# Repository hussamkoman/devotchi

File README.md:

<h1 align="center">Devotchi</h1>

<p align="center">
  <b>A desk pet for your coding agent.</b><br>
  See what Claude Code is doing and answer it with three buttons.
</p>

When Claude Code needs you, Devotchi buzzes and shows the request. You allow,
deny or answer from across the desk. Between requests, its pet shows how the
work is going.

> Devotchi never decides on its own. Only a button press allows or denies.
> If nobody answers, Claude Code's normal terminal prompt takes over.

## Features

- **Approvals.** See the exact command and its risk. Allow, deny, allow for this
  session, or send it to the terminal. High-risk commands need a hold.
- **Questions and plans.** Answer Claude's questions and approve or revise its plans.
- **A pet with moods.** 11 moods and 5 reactions, driven by Claude Code hooks.
- **Clock face** while idle, **Showcase mode** for demos, real **sleep modes**
  and battery support.
- **Self-hosted.** A small server on your PC, a local dashboard, optional
  multi-user hosting.

## Screens

<table>
  <tr>
    <td align="center"><br><sub>Decision menu</sub></td>
    <td align="center"><br><sub>Question from Claude</sub></td>
    <td align="center"><br><sub>Plan approval</sub></td>
  </tr>
  <tr>
    <td align="center"><br><sub>Tests passed</sub></td>
    <td align="center"><br><sub>Clock face</sub></td>
    <td align="center"><br><sub>Settings</sub></td>
  </tr>
</table>

Screenshots are taken from the real device. The full design is in [docs/design](docs/design/index.html).

## Pets

Each pet is one JSON file in [`pets/`](pets/README.md). Adding a pet needs no code.

| | |
|---|---|
|  | **Devo** (default)<br>The ghost from the PCB silkscreen. Its antenna and chip light show the mood. |
|  | **Mochi**<br>A soft square with an antenna. |
|  | **Ember**<br>A small jade dragon. Wings, tail, smoke and fire show the mood. |
|  | **Sprout**<br>An egg with a leaf. Install it from the dashboard. |

Shown in the happy, focused and sleeping moods.

## How it works

```
Claude Code ──hooks──▶ Devotchi server ──Wi-Fi──▶ Devotchi device
  (your PC)            (Node, SQLite)              (ESP32-S3 + LCD)
                            │
                            └──▶ dashboard (browser)
```

1. `devotchi setup` adds HTTP hooks to Claude Code.
2. Requests go to the server, which shows them on the device and the dashboard.
3. You press a button. The device sends a heartbeat while it shows a request,
   so the server knows it is alive.
4. If nobody answers in time (default 30 s), or no device is online, Claude
   Code shows its own prompt.

## Quick start

Needs Node 22.13+ and pnpm 10.

```bash
pnpm install && pnpm run build
alias devotchi="node $PWD/packages/client/dist/cli.js"

devotchi start --local --lan   # server on :8080, dashboard on 127.0.0.1:3456
devotchi setup                 # add the hooks to this project
```

Then set up the device:

1. **Wi-Fi:** install the **ESP BLE Provisioning** app and scan the QR code
   *inside the app*. Your phone's camera app can't do this.
2. **Server:** the device connects to `ws://<your PC>:8080`. Change it with
   `server ws://<ip>:8080` on the USB console.
3. **Pair:** run `devotchi pair <CODE>` with the code on the screen.

For a hosted server with TLS and accounts, see [docs/deploy.md](docs/deploy.md).

## Buttons

| | Left | Middle | Right |
|---|---|---|---|
| **Home** | Poke | Recent activity · hold: menu | Pat |
| **Request** | Deny | Hold: more options | Allow (high risk: hold) |
| **Settings** | Up · hold: back | Next | Open |

Any press wakes the device and does nothing else.

## CLI

```bash
devotchi start | setup | pair <CODE> | status | doctor
devotchi devices | pets | mode [ask|desk] | hold [seconds]
devotchi notify <event> | run -- <cmd> | sim | mcp | login | config
```

Run `devotchi doctor` when something doesn't work. Full list: [CLAUDE.md](CLAUDE.md#client-cli).

## Hardware

- ESP32-S3-MINI-1 (Wi-Fi, BLE, 4 MB flash, 2 MB PSRAM)
- 2.0" 320x240 IPS display (ST7789)
- 3 buttons, vibration motor, status LED
- LiPo battery with USB-C charging

Details: [hardware/README.md](hardware/README.md).

<br clear="right">

## Development

```bash
pnpm test && pnpm run typecheck && pnpm run lint
```

The firmware is plain C on ESP-IDF 6.0 with LVGL 9. Building, flashing and
tests: [firmware/README.md](firmware/README.md).

| Folder | What's in it |
|---|---|
| `firmware/` | ESP32-S3 firmware and host tests |
| `packages/` | `shared` protocol, `server`, `client` (CLI, MCP, dashboard) |
| `pets/` | Pet JSON files |
| `docs/` | [Architecture](docs/architecture.md), [protocol](docs/protocol.md), [design](docs/design/index.html) |
| `hardware/`, `case/` | PCB and enclosure |

Open work: [TODO.md](TODO.md).

## License

[MIT](LICENSE)

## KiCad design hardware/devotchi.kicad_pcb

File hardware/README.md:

# Hardware Design

## PCB

## Device Variants

### Portable WiFi+BLE (current)
- ESP32-S3-MINI-1 with integrated PCB antenna
- HS20HS072RX 2.0" color TFT LCD (ST7789, 320x240, IPS)
- LiPo battery, USB-C charging
- 3 buttons (approve, reject, action)
- Status LED, vibration motor
- Connects to server via WiFi, or to phone via BLE

### Portable Cellular (planned)
- Same form factor as WiFi+BLE version
- Additional cellular modem (MCU TBD — may use same ESP32-S3 + SIM module, or different MCU)
- SIM/eSIM support (provider TBD)
- Works standalone anywhere with cell coverage

### Desktop (planned)
- USB-powered (no battery needed)
- Potentially larger display
- Same ESP32-S3-MINI-1, connects via USB serial or WiFi

---

## Parts

See [purchase-list.md](purchase-list.md) for the complete BOM with LCSC part numbers and sourcing info.

### MCU: ESP32-S3-MINI-1-N4R2

| Spec | Value |
|---|---|
| Part number | ESP32-S3-MINI-1-N4R2 (4MB flash, 2MB PSRAM) |
| CPU | Dual-core Xtensa LX7 @ 240 MHz |
| SRAM | 512 KB + 2MB PSRAM |
| WiFi | 802.11 b/g/n, 2.4 GHz |
| Bluetooth | BLE 5.0 |
| Antenna | Integrated PCB antenna |
| Module dimensions | 15.4 x 20.5 x 2.4 mm |
| Operating voltage | 3.0 - 3.6V |

**Datasheets:** [Module](../docs/mcu/ESP32-S3-MINI-1_datasheet.pdf) | [SoC](../docs/mcu/ESP32-S3_SoC_datasheet.pdf)

**Why N4R2:** PSRAM needed for display framebuffers — 320x240 RGB565 = 150KB per frame, double buffering needs 300KB. Without PSRAM, internal 512KB SRAM can't fit framebuffers + WiFi stack + application.

### Display: HS20HS072RX 2.0" Color TFT LCD

| Spec | Value |
|---|---|
| Manufacturer | HS (Shenzhen Hansheng) |
| Part number | HS20HS072RX |
| LCSC | C5329582 |
| Driver IC | ST7789T3 |
| Size | 2.0 inches diagonal |
| Resolution | 320 x 240 pixels (QVGA) |
| Colors | 262K (RGB666) |
| Pixel pitch | 0.151 x 0.153 mm |
| Active area | 40.80 x 30.60 mm |
| Module size | 51.80 x 36.20 mm |
| Interface | SPI (4-wire) |
| Operating voltage | IOVCC 1.65-3.3V, VCI 2.4-3.3V |
| Backlight | 4 white LEDs in parallel, 80mA max |
| Backlight forward voltage | 3.0V typical (2.8-3.2V) |
| Sleep current | ~30 uA (SLPIN command) |
| Viewing angle | ALL directions (IPS) |
| Contrast ratio | 300:1 typical |
| Connector | 12-pin FPC, 0.5mm pitch |
| Connection type | COG + FPC |

**Datasheet:** [HS20HS072RX datasheet](../docs/display/HS20HS072RX_datasheet.pdf)

**Source:** [LCSC/JLCPCB C5329582](https://www.lcsc.com/product-detail/lcd-screen_hs-hs20hs072rx_C5329582.html) — $3.70 (1+), $2.49 (100+), 1687 in stock.

**Why this part:**
- Full RGB color — expressive Tamagotchi character (red angry, green happy, etc.)
- 320x240 resolution — excellent detail for pixel art and text
- IPS viewing angle — looks good from any direction (critical for handheld)
- Runs entirely on 3.3V — no boost converter needed (unlike OLED panels needing 12V VCC)
- ST7789 has first-class ESP-IDF support via built-in `esp_lcd` driver
- $2.49 at volume with 1600+ stock — cheap and available
- 12-pin FPC is simple to wire (vs 30-pin for OLED panels)
- Backlight can be PWM-dimmed via MOSFET for power saving

**FPC pinout:**

| Pin | Symbol | Description |
|---|---|---|
| 1 | GND | Power ground |
| 2 | CS | Chip select (active low) |
| 3 | RS (DC) | Data/command select |
| 4 | SCL | SPI clock |
| 5 | SDA | SPI data (MOSI) |
| 6 | RST | Reset (active low) |
| 7 | NC | No connect |
| 8 | IOVCC | I/O logic supply (3.3V) |
| 9 | VCC | Panel power supply (3.3V) |
| 10 | A | Backlight LED anode |
| 11 | K | Backlight LED cathode |
| 12 | GND | Power ground |

### Backlight Dimming Circuit

Backlight driven from +BATT (3.7-4.2V) through 22Ω resistor + AO3400A N-ch MOSFET, PWM-controlled by ESP32.

**Why +BATT instead of 3.3V:** LEDs have Vf = 3.0V. Only 0.3V headroom from 3.3V — poor regulation. +BATT gives 0.7-1.2V headroom.

**Circuit:** `+BATT → R (22Ω) → LED anode → LED cathode → MOSFET drain → GND`, gate driven by DISP_BL GPIO.

**Current at different battery voltages:**
- 4.2V (full): ~55mA | 3.7V (nominal): ~32mA | 3.4V (low): ~18mA

**Firmware:** PWM at 1kHz+. Sleep: SLPIN (0x10) + duty=0. Wake: duty>0 + SLPOUT (0x11), wait 120ms.

### Firmware Graphics Library

**Recommended: ESP-IDF native `esp_lcd` + LovyanGFX**

- `esp_lcd` provides the built-in ST7789 panel driver for SPI initialization
- LovyanGFX provides sprite-based graphics, text rendering, and animations
- LovyanGFX supports ESP-IDF natively (not Arduino-only)
- Supports DMA transfers for background rendering
- ST7789 sleep commands (SLPIN/SLPOUT) supported for power management
- Alternative: LVGL if more complex UI widgets are needed later

### Power Chain

USB-C → TP4056 (charger) → DW01A+FS8205A (protection) → ME6211 (3.3V LDO) → ESP32-S3 + display

**Datasheets:** [TP4056](../docs/power/TP4056_datasheet.pdf) | [DW01A](../docs/power/DW01A_datasheet.pdf) | [FS8205A](../docs/power/FS8205A_datasheet.pdf) | [ME6211](../docs/power/ME6211_datasheet.pdf)

**Key design notes:**
- TP4056 charge current set by R205 (3kΩ → ~330mA charge rate)
- DW01A+FS8205A: standard LiPo protection pair, back-to-back MOSFETs in battery ground path
- ME6211 LDO: 100mV dropout — at low battery (<3.4V) output sags below 3.3V, acceptable for MVP
- USB-C CC1/CC2 pull-downs: 5.1kΩ each for proper USB-C detection

### Buttons

3 tactile switches with hardware debounce (10kΩ pull-up + 100nF cap per button). Active low, pressed = GND. Any button press wakes from deep sleep.

| Button | Function |
|---|---|
| Approve | Accept approval/permission requests |
| Reject | Reject approval/permission requests |
| Action | Context-dependent: scroll, open menu, poke pet |

### Feedback

- **Debug LED** (green 0603) — GPIO direct drive through 150Ω resistor. Dev/debug only.
- **Vibration motor** (6mm coin, 3V) — AO3400A MOSFET driver + 1N5819W flyback diode. PWM-capable. Connected via solder pads.

---

## Pin Assignment

**Strapping pins to avoid:** GPIO0 (boot mode), GPIO3 (JTAG source, floating), GPIO45 (VDD_SPI), GPIO46 (boot mode). These are sampled at reset and should not have external loads that could affect their default state during boot.

| Function | ESP32-S3 GPIO | Notes |
|---|---|---|
| **SPI Display** | | |
| DISP_SCLK | GPIO 12 | SPI clock |
| DISP_MOSI | GPIO 11 | SPI data |
| DISP_CS | GPIO 10 | Chip select |
| DISP_DC | GPIO 9 | Data/command select |
| DISP_RST | GPIO 8 | Reset |
| DISP_BL | GPIO 13 | PWM via MOSFET to backlight cathode |
| **Buttons** | | |
| BTN_APPROVE | GPIO 4 | Pull-up, active low |
| BTN_REJECT | GPIO 5 | Pull-up, active low |
| BTN_ACTION | GPIO 6 | Pull-up, active low |
| **Feedback** | | |
| LED_PWM | GPIO 38 | PWM for brightness control |
| MOTOR_EN | GPIO 37 | Via N-channel MOSFET |
| **Power status** | | |
| PWR_CHRG | GPIO 18 | Low = charging |
| PWR_STDBY | GPIO 17 | Low = charge complete |
| BAT_ADC | GPIO 1 | Via voltage divider for battery level |
| **Future (unused, reserved)** | | |
| I2S BCLK | GPIO 15 | For microphone (voice commands) |
| I2S WS | GPIO 16 | For microphone |
| I2S DIN | GPIO 2 | For microphone (GPIO 17 used by PWR_STDBY) |

---

## Power Budget (estimated)

| State | ESP32-S3 | Display | Total | Battery life (500mAh) |
|---|---|---|---|---|
| **Active** (WiFi on, display on, backlight 100%) | ~80 mA | ~60 mA | ~140 mA | ~3.6 hours |
| **Idle** (WiFi connected, backlight 25%) | ~20 mA | ~15 mA | ~35 mA | ~14 hours |
| **Light sleep** (WiFi off, backlight off, LCD sleep) | ~2 mA | ~0.03 mA | ~2 mA | ~250 hours |
| **Deep sleep** (everything off) | ~8 uA | ~30 uA | ~38 uA | ~1.5 years |

Real-world usage will be a mix — display on for a few seconds when events arrive, then back to sleep. Expected practical battery life: **2-5 days** with typical AI coding session activity.

---

## Power Management Strategy

1. **Normal operation**: WiFi connected, display off. ESP32 in light sleep between events.
2. **Event arrives** (via WiFi): Wake up, turn on display, show status/approval, vibrate if needed.
3. **Approval request**: Display stays on with countdown timer until user responds or timeout.
4. **No activity for N minutes**: Enter deep sleep. Wake on any button press.
5. **Deep sleep**: Everything off. Battery lasts weeks/months.
6. **Display auto-off**: Display turns off after 30 seconds of no new events (configurable).

---

## PCB Design Notes

- **Single PCB** — power management and logic on one board
- Power section (TP4056, ME6211, USB-C, battery connector) on one side, logic section (ESP32, display connector, buttons) on the other
- Ground plane between sections
- ESP32-S3-MINI-1 antenna keepout zone respected (no copper/ground under antenna area)
- Display connects via 12-pin 0.5mm FPC cable (AFC01-S12FCA-00 connector)
- USB-C connector: 16-pin mid-mount type with D+/D- connected to ESP32-S3 USB OTG pins for firmware updates and serial communication
- Battery connector: JST-PH 2-pin SMD (standard for small LiPo, LCSC C7433648)
- Test points: 3.3V, +BATT, GND, UART TX/RX

---

## Enclosure

- 3D printed (material TBD: PLA, ABS, or PETG)
- Size determined after PCB layout and LiPo selection
- Rough estimate: ~50 x 40 x 20mm (similar to original Tamagotchi)
- Cutouts for: display window, 4 buttons, USB-C port, LED light pipe
- Optional clip or lanyard hole for portability

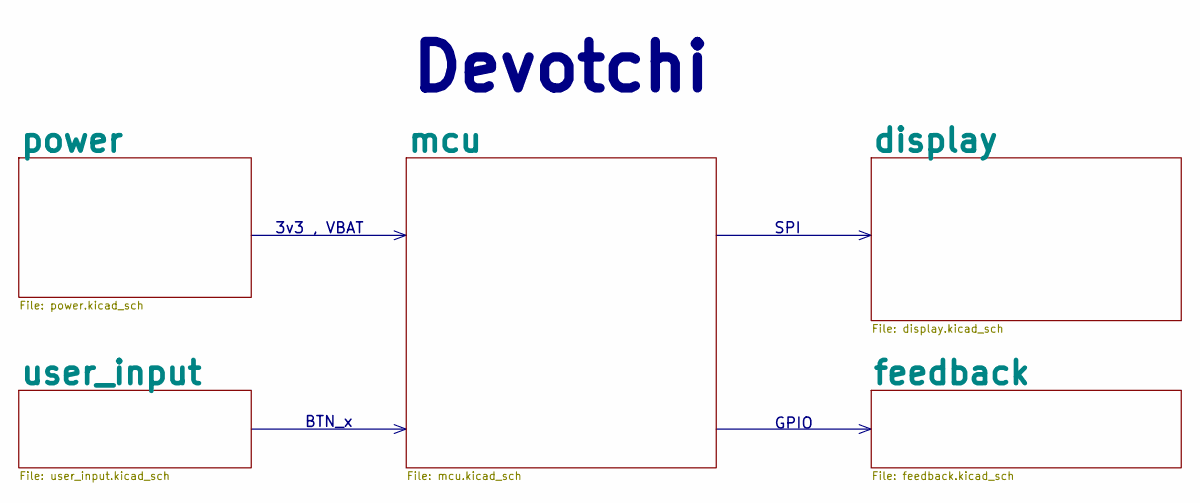
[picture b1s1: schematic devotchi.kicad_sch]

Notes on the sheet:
Devotchi
3v3 , VBAT
GPIO
SPI
BTN_x

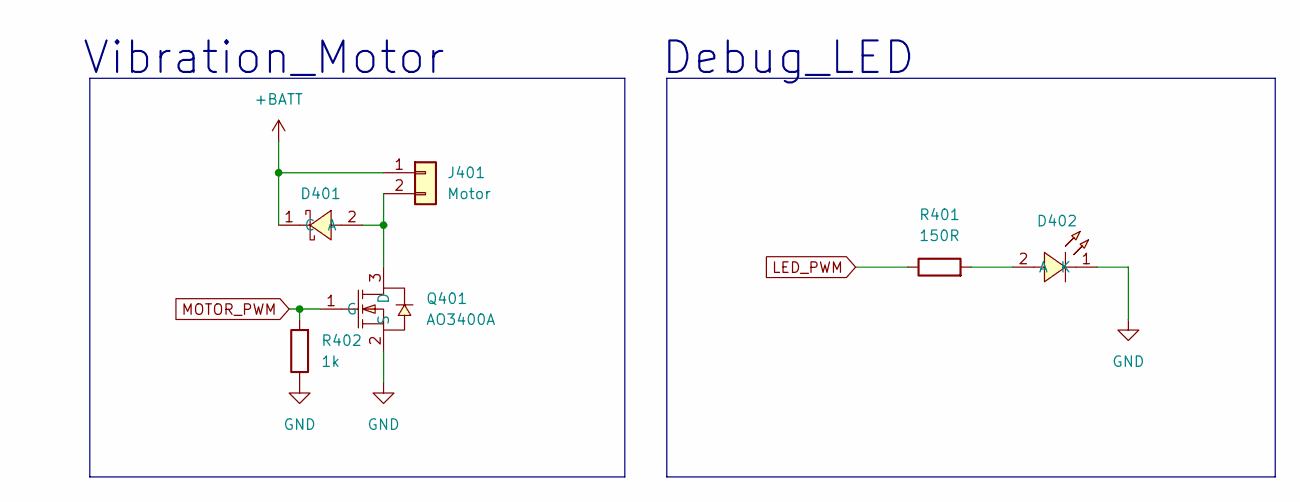
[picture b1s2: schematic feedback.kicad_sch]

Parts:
D401: 1N5819W S4_C42441798; SOD-123_L2.7-W1.6-LS3.7-RD; LCSC Part C42441798
D402: FC-1608G1-520; LED0603-RD; LCSC Part C19189745
J401: Motor; PinHeader_1x02_P2.54mm_Vertical_SMD_Pin1Right
Q401: AO3400A; SOT-23-3_L2.9-W1.3-P1.90-LS2.4-BR; LCSC Part C20917
R401: 150R; R_0603_1608Metric_Pad0.98x0.95mm_HandSolder; LCSC Part C22808
R402: 1k; R_0603_1608Metric_Pad0.98x0.95mm_HandSolder; LCSC Part C22808

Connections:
+BATT: D401.1 (C), J401.1; also elsewhere on the board
GND: D402.1 (K), Q401.2 (S), R402.1; also elsewhere on the board
LED_PWM: R401.1; also elsewhere on the board
MOTOR_PWM: Q401.1 (G), R402.2; also elsewhere on the board
unnamed: D401.2 (A), J401.2, Q401.3 (D)
unnamed: D402.2 (A), R401.2

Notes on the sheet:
Vibration_Motor
Debug_LED

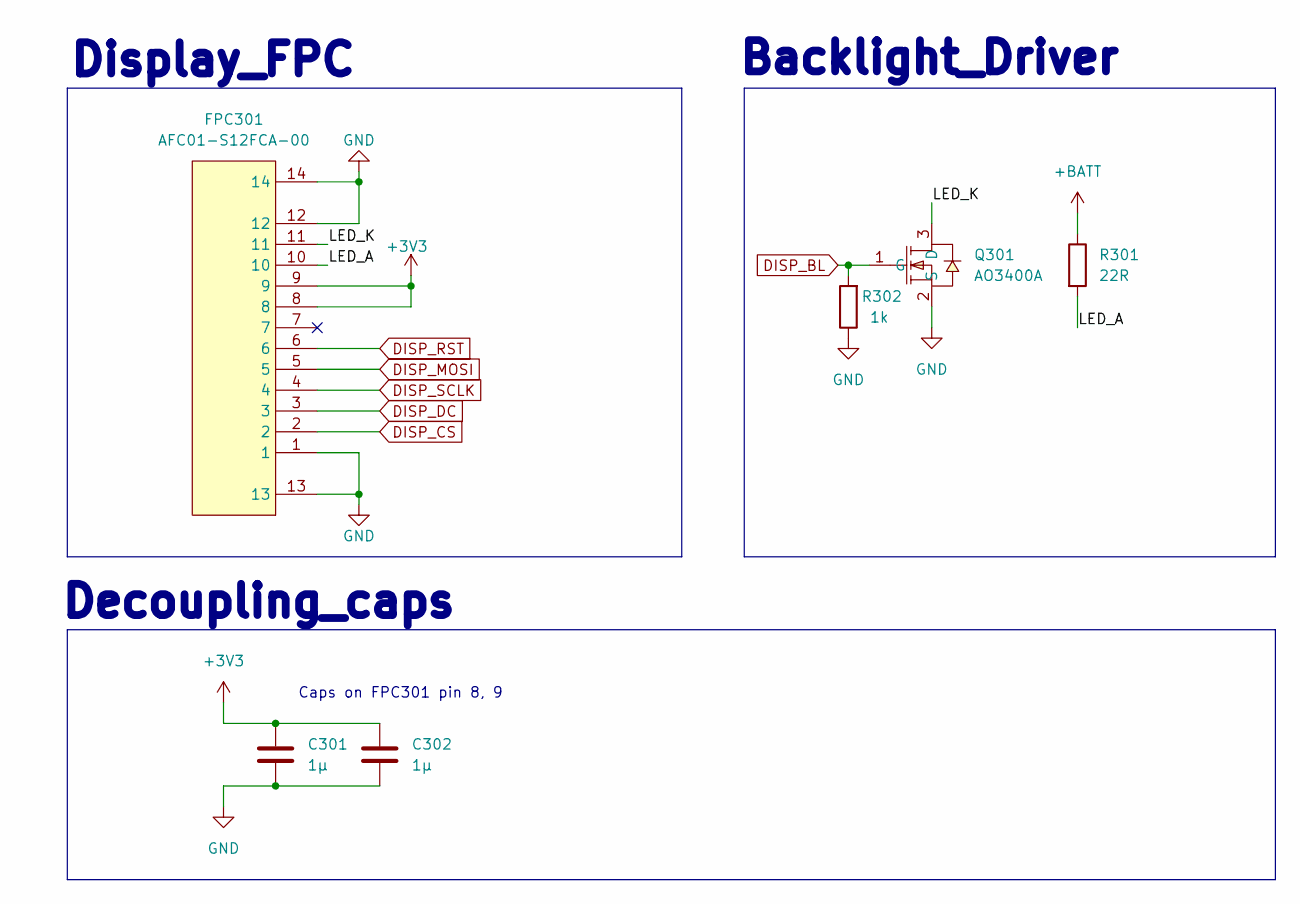
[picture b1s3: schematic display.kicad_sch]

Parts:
C301, C302: 1µ; C_0603_1608Metric_Pad1.08x0.95mm_HandSolder; LCSC Part C15849
FPC301: AFC01-S12FCA-00; FPC-SMD_AFC01-S12FCA-00; LCSC Part C262661
Q301: AO3400A; SOT-23-3_L2.9-W1.3-P1.90-LS2.4-BR; LCSC Part C20917
R301: 22R; R_0603_1608Metric_Pad0.98x0.95mm_HandSolder; LCSC Part C23345
R302: 1k; R_0603_1608Metric_Pad0.98x0.95mm_HandSolder; LCSC Part C22808

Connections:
+3V3: C301.1, C302.1, FPC301.8, FPC301.9; also elsewhere on the board
+BATT: R301.1; also elsewhere on the board
/display/LED_A: FPC301.10, R301.2
/display/LED_K: FPC301.11, Q301.3 (D)
DISP_BL: Q301.1 (G), R302.2; also elsewhere on the board
DISP_CS: FPC301.2; also elsewhere on the board
DISP_DC: FPC301.3; also elsewhere on the board
DISP_MOSI: FPC301.5; also elsewhere on the board
DISP_RST: FPC301.6; also elsewhere on the board
DISP_SCLK: FPC301.4; also elsewhere on the board
GND: C301.2, C302.2, FPC301.1, FPC301.12, FPC301.13, FPC301.14, Q301.2 (S), R302.1; also elsewhere on the board

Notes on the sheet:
Decoupling_caps
Caps on FPC301 pin 8, 9
Display_FPC
Backlight_Driver

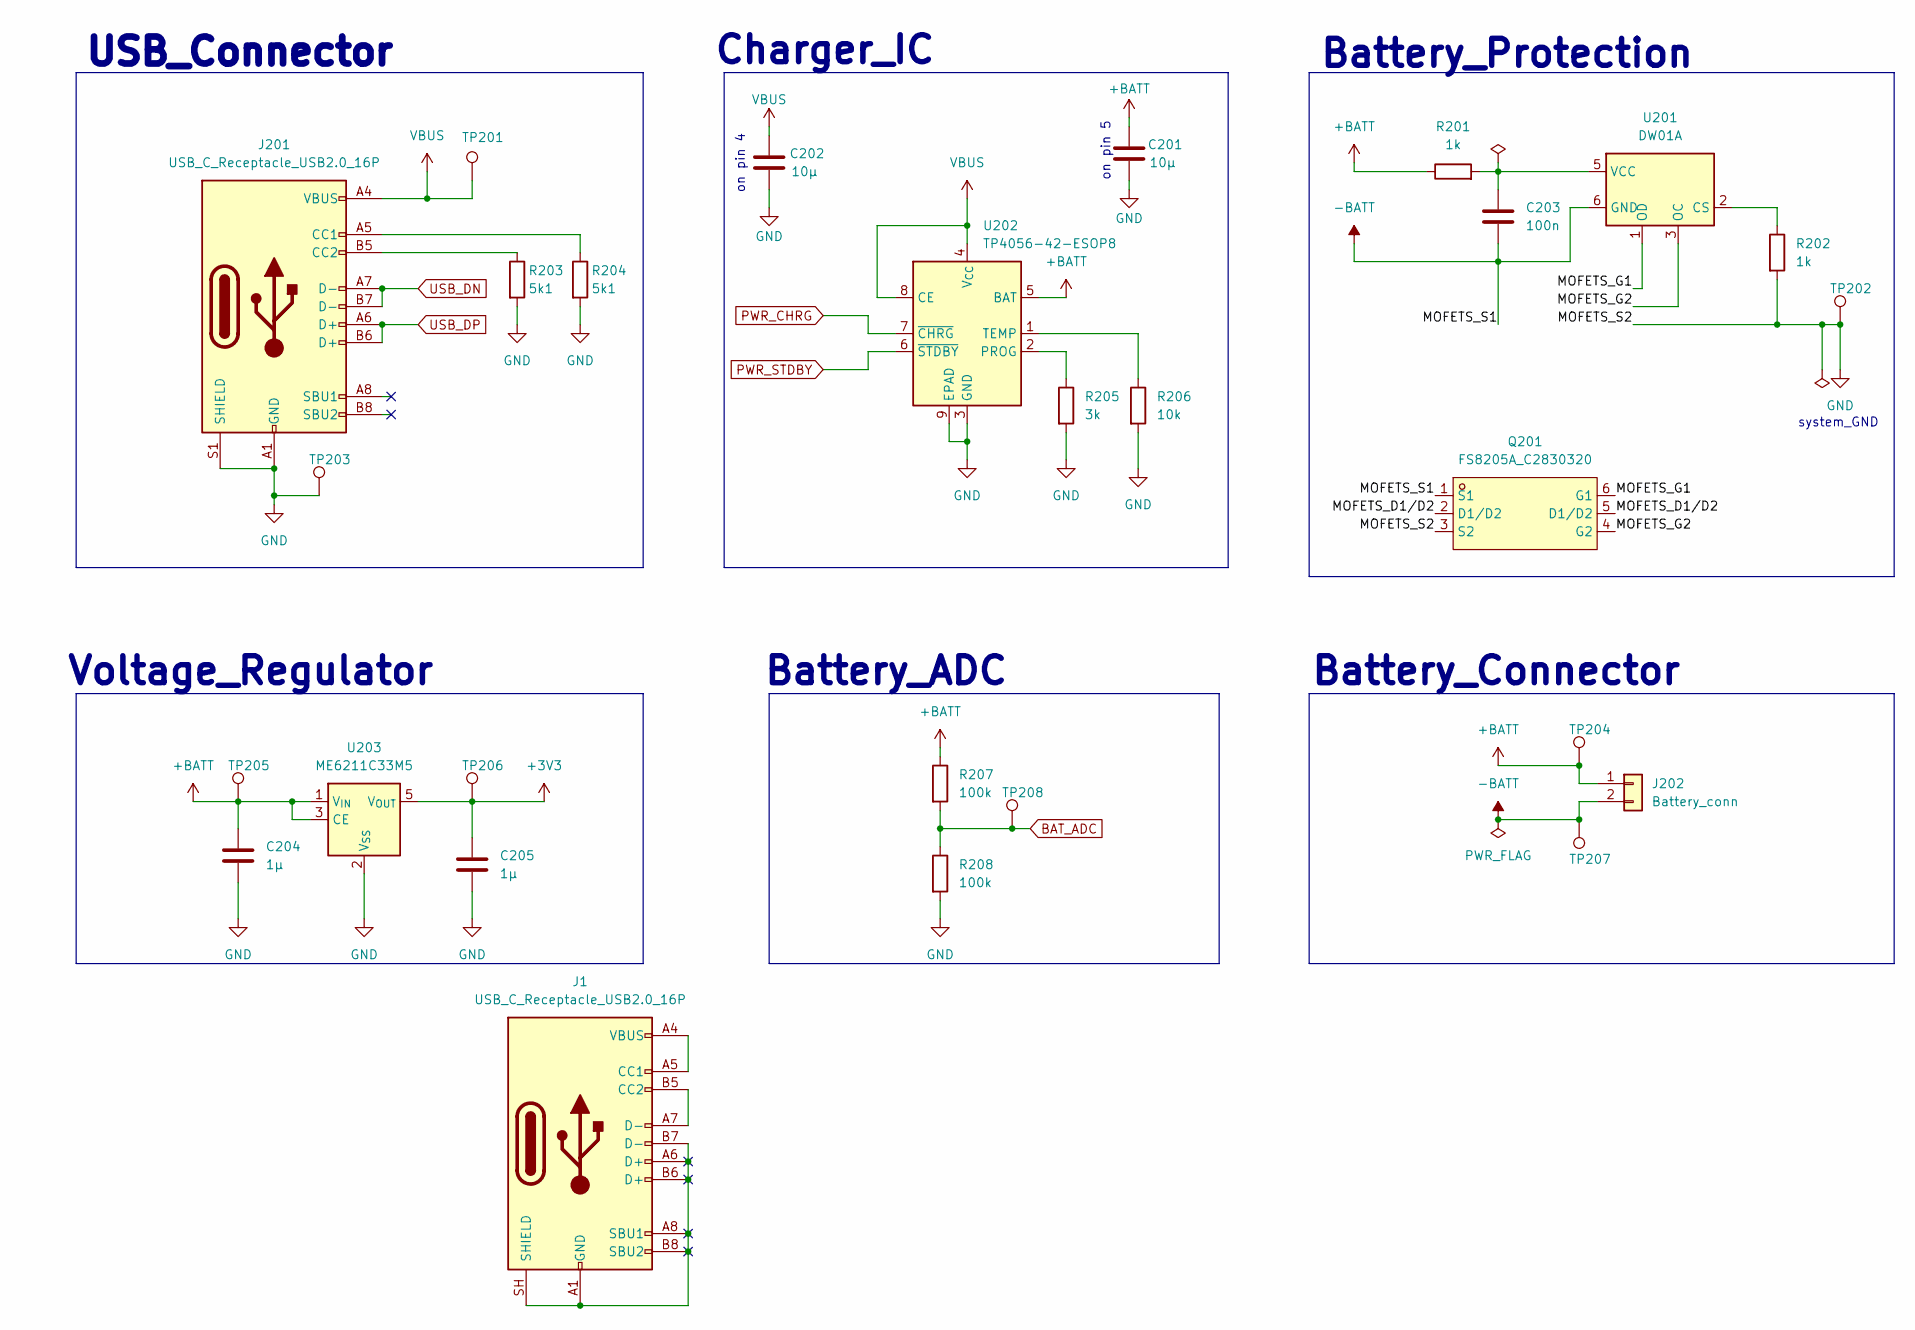
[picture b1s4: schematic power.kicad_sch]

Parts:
C201, C202: 10µ; C_0805_2012Metric_Pad1.18x1.45mm_HandSolder; LCSC Part C15850
C203: 100n; C_0603_1608Metric_Pad1.08x0.95mm_HandSolder; LCSC Part C14663
C204, C205: 1µ; C_0603_1608Metric_Pad1.08x0.95mm_HandSolder; LCSC Part C15849
J1: USB_C_Receptacle_USB2.0_16P; USB_C_Receptacle_HRO_TYPE-C-31-M-12
J201: USB_C_Receptacle_USB2.0_16P; USB_C_Receptacle_HRO_TYPE-C-31-M-12; LCSC Part C165948
J202: Battery_conn; JST_PH_S2B-PH-SM4-TB_1x02-1MP_P2.00mm_Horizontal; LCSC Part C7433648
Q201: FS8205A_C2830320; SOT-23-6_L2.9-W1.6-P0.95-LS2.8-BR; LCSC Part C2830320
R201, R202: 1k; R_0603_1608Metric_Pad0.98x0.95mm_HandSolder; LCSC Part C21190
R203, R204: 5k1; R_0603_1608Metric_Pad0.98x0.95mm_HandSolder; LCSC Part C23186
R205: 3k; R_0603_1608Metric_Pad0.98x0.95mm_HandSolder; LCSC Part C4211
R206: 10k; R_0603_1608Metric_Pad0.98x0.95mm_HandSolder; LCSC Part C25804
R207, R208: 100k; R_0603_1608Metric_Pad0.98x0.95mm_HandSolder; LCSC Part C25803
TP201, TP202, TP203, TP204, TP205, TP206, TP207, TP208: TestPoint; TestPoint_Pad_D1.0mm
U201: DW01A; SOT-23-6; LCSC Part C351410
U202: TP4056-42-ESOP8; SOIC-8-1EP_3.9x4.9mm_P1.27mm_EP2.41x3.3mm_ThermalVias; LCSC Part C725790
U203: ME6211C33M5; SOT-23-5; LCSC Part C82942

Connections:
+3V3: C205.1, TP206.1 (1_1), U203.5 (V_{OUT}); also elsewhere on the board
+BATT: C201.1, C204.1, J202.1, R201.1, R207.1, TP204.1 (1_1), TP205.1 (1_1), U202.5 (BAT), U203.1 (V_{IN}), U203.3 (CE); also elsewhere on the board
-BATT: C203.2, J202.2, Q201.1 (S1), TP207.1 (1_1), U201.6 (GND)
/power/MOFETS_D1/D2: Q201.2 (D1/D2), Q201.5 (D1/D2)
/power/MOFETS_G1: Q201.6 (G1), U201.1 (OD)
/power/MOFETS_G2: Q201.4 (G2), U201.3 (OC)
BAT_ADC: R207.2, R208.1, TP208.1 (1_1); also elsewhere on the board
GND: C201.2, C202.2, C204.2, C205.2, J201.A1 (GND), J201.A12 (GND), J201.B1 (GND), J201.B12 (GND), J201.S1 (SHIELD), Q201.3 (S2), R202.2, R203.2, R204.2, R205.2, R206.2, R208.2, TP202.1 (1_1), TP203.1 (1_1), U202.3 (GND), U202.9 (EPAD), U203.2 (V_{SS}); also elsewhere on the board
unnamed: J1.A1 (GND), J1.A6 (D+), J1.A8 (SBU1), J1.A12 (GND), J1.B1 (GND), J1.B6 (D+), J1.B7 (D-), J1.B8 (SBU2), J1.B12 (GND), J1.SH (SHIELD)
unnamed: J1.A4 (VBUS), J1.A5 (CC1), J1.A9 (VBUS), J1.B4 (VBUS), J1.B9 (VBUS)
unnamed: J1.A7 (D-), J1.B5 (CC2)
unnamed: J201.A5 (CC1), R204.1
unnamed: J201.B5 (CC2), R203.1
unnamed: R202.1, U201.2 (CS)
unnamed: C203.1, R201.2, U201.5 (VCC)
unnamed: R205.1, U202.2 (PROG)
unnamed: R206.1, U202.1 (TEMP)
PWR_CHRG: U202.7 (~CHRG); also elsewhere on the board
PWR_STDBY: U202.6 (~STDBY); also elsewhere on the board
USB_DN: J201.A7 (D-), J201.B7 (D-); also elsewhere on the board
USB_DP: J201.A6 (D+), J201.B6 (D+); also elsewhere on the board
VBUS: C202.1, J201.A4 (VBUS), J201.A9 (VBUS), J201.B4 (VBUS), J201.B9 (VBUS), TP201.1 (1_1), U202.4 (V_{CC}), U202.8 (CE)

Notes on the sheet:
on pin 4
system_GND
Battery_Connector
Battery_Protection
USB_Connector
on pin 5
Battery_ADC
Voltage_Regulator
Charger_IC

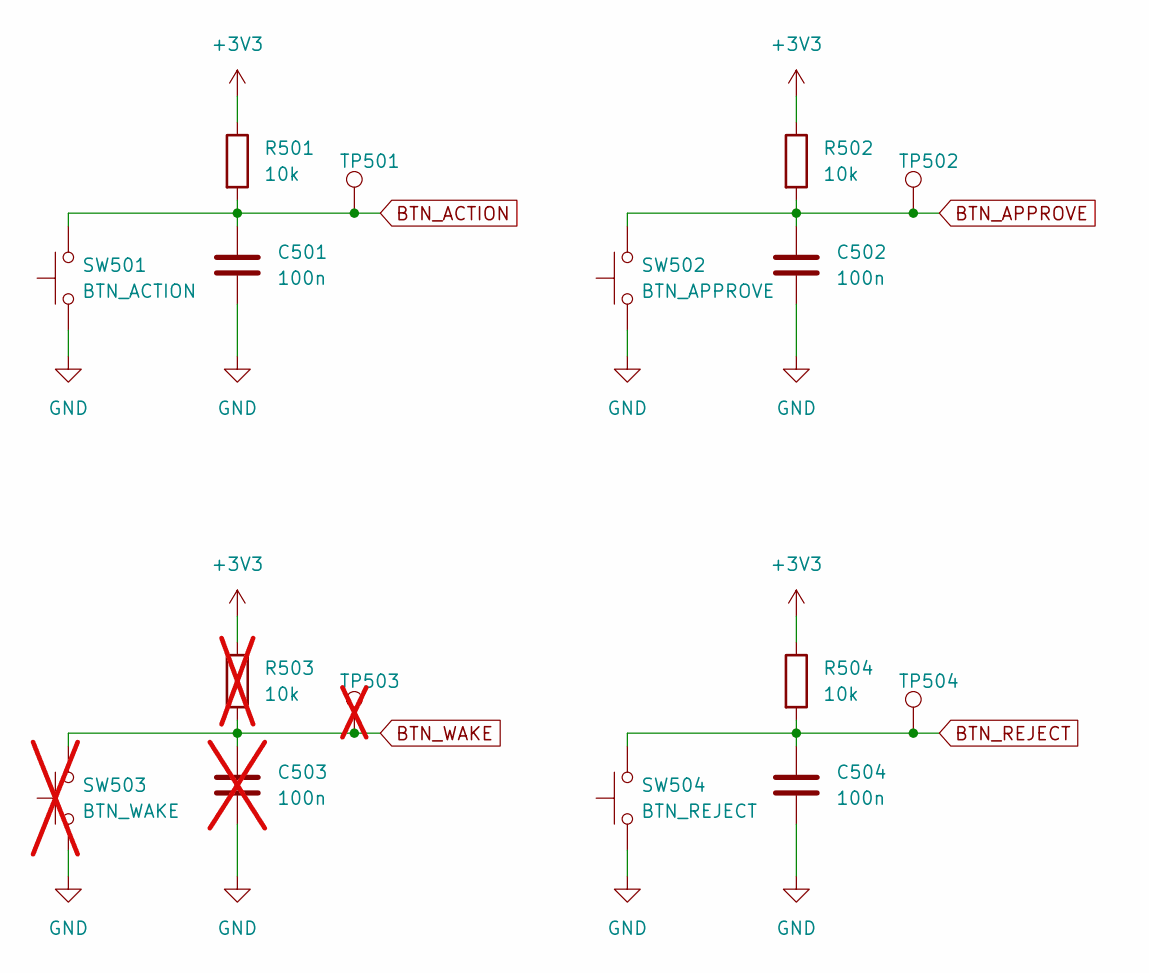
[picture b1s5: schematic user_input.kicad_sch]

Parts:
C501, C502, C504: 100n; C_0603_1608Metric_Pad1.08x0.95mm_HandSolder; LCSC Part C14663
C503: 100n; C_0603_1608Metric_Pad1.08x0.95mm_HandSolder; LCSC Part C14663; not fitted
R501, R502, R504: 10k; R_0603_1608Metric_Pad0.98x0.95mm_HandSolder; LCSC Part C25804
R503: 10k; R_0603_1608Metric_Pad0.98x0.95mm_HandSolder; LCSC Part C25804; not fitted
SW501: BTN_ACTION; SW_Push_1P1T_XKB_TS-1187A; LCSC Part C318884
SW502: BTN_APPROVE; SW_Push_1P1T_XKB_TS-1187A; LCSC Part C318884
SW503: BTN_WAKE; SW_Push_1P1T_XKB_TS-1187A; LCSC Part C318884; not fitted
SW504: BTN_REJECT; SW_Push_1P1T_XKB_TS-1187A; LCSC Part C318884
TP501, TP502, TP504: TestPoint; TestPoint_Pad_D1.0mm
TP503: TestPoint; TestPoint_Pad_D1.0mm; not fitted

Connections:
+3V3: R501.1, R502.1, R503.1, R504.1; also elsewhere on the board
BTN_ACTION: C501.1, R501.2, SW501.2, TP501.1 (1_1); also elsewhere on the board
BTN_APPROVE: C502.1, R502.2, SW502.2, TP502.1 (1_1); also elsewhere on the board
BTN_REJECT: C504.1, R504.2, SW504.2, TP504.1 (1_1); also elsewhere on the board
GND: C501.2, C502.2, C503.2, C504.2, SW501.1, SW502.1, SW503.1, SW504.1; also elsewhere on the board
unnamed: C503.1, R503.2, SW503.2, TP503.1

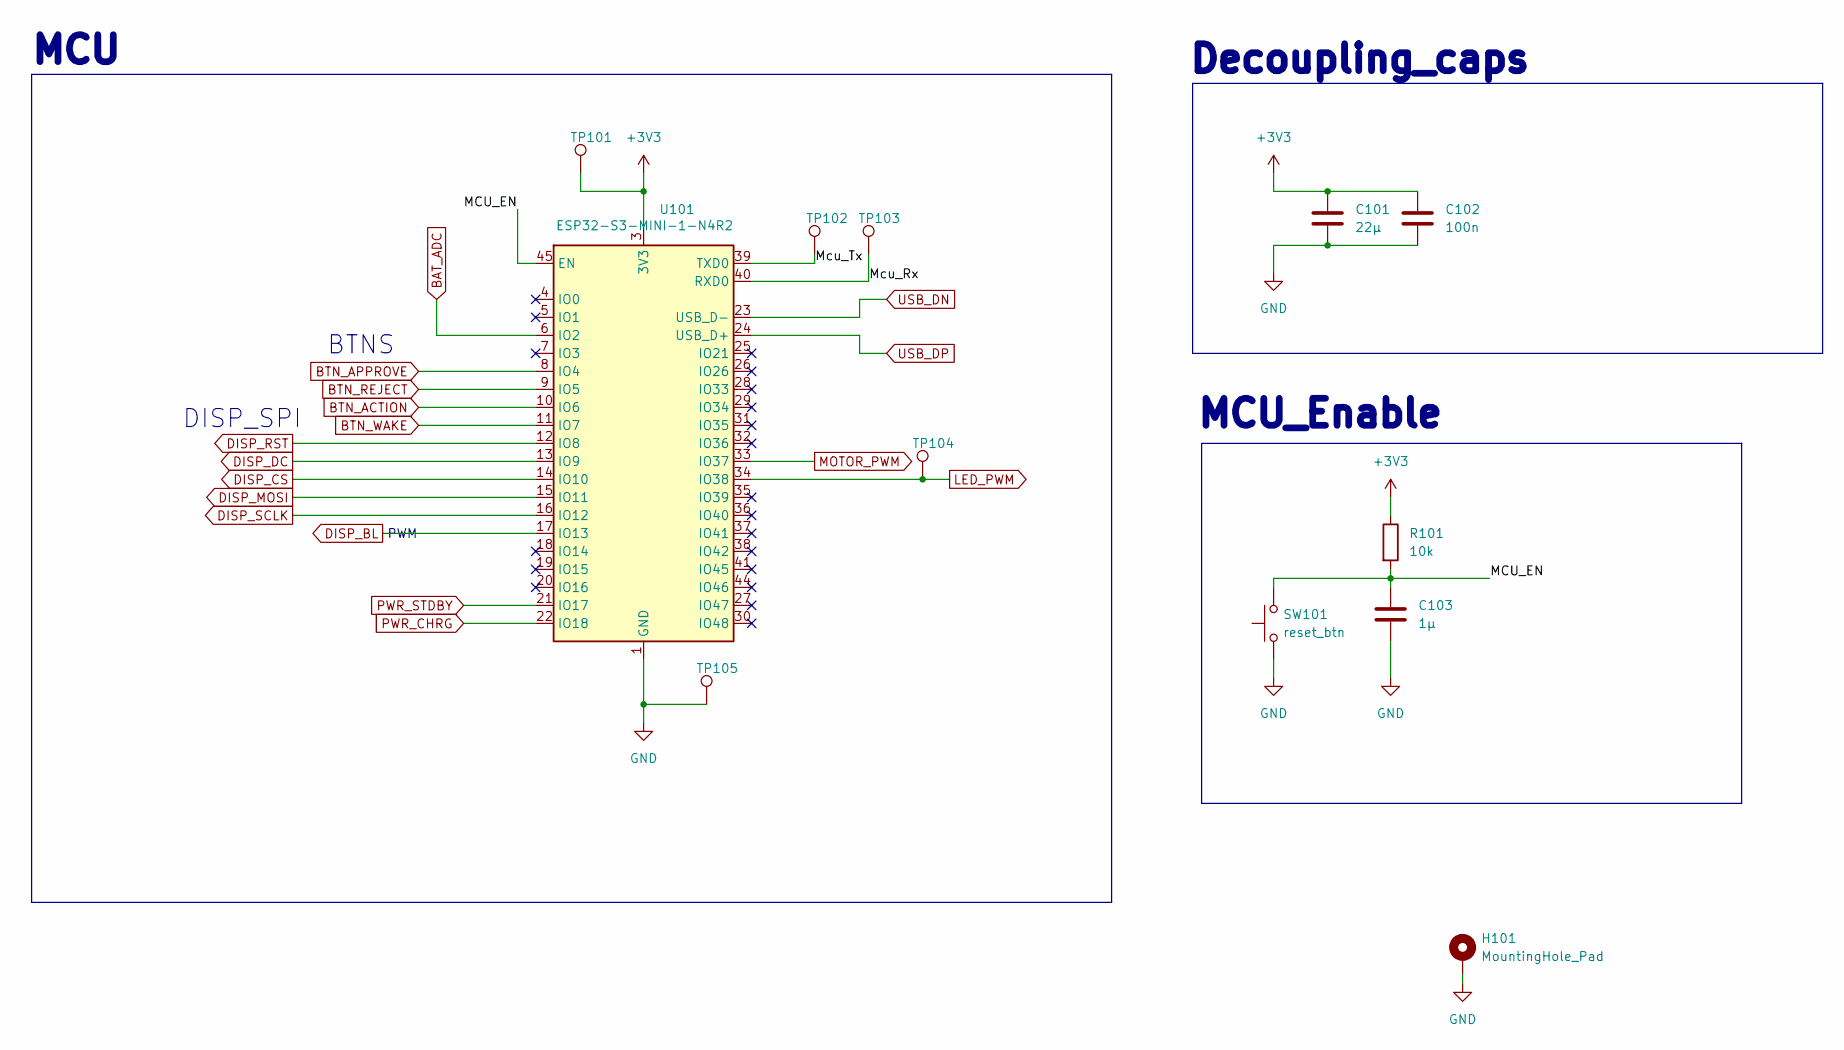
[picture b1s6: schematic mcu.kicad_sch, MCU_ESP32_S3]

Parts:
C101: 22µ; C_0805_2012Metric_Pad1.18x1.45mm_HandSolder; LCSC Part C45783
C102: 100n; C_0603_1608Metric_Pad1.08x0.95mm_HandSolder; LCSC Part C14663
C103: 1µ; C_0603_1608Metric_Pad1.08x0.95mm_HandSolder; LCSC Part C15849
H101: MountingHole_Pad; MountingHole_2.2mm_M2_DIN965_Pad
R101: 10k; R_0603_1608Metric_Pad0.98x0.95mm_HandSolder; LCSC Part C25804
SW101: reset_btn; SW_Push_1P1T_XKB_TS-1187A; LCSC Part C318884
TP101, TP104, TP105: TestPoint; TestPoint_Pad_D1.0mm
TP102: Tx; TestPoint_Pad_D1.0mm
TP103: Rx; TestPoint_Pad_D1.0mm
U101: ESP32-S3-MINI-1-N4R2; ESP32-S2-MINI-1; LCSC Part C3013941

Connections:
+3V3: C101.1, C102.1, R101.1, TP101.1 (1_1), U101.3 (3V3); also elsewhere on the board
/mcu/MCU_EN: C103.1, R101.2, SW101.2, U101.45 (EN)
/mcu/Mcu_Rx: TP103.1 (1_1), U101.40 (RXD0)
/mcu/Mcu_Tx: TP102.1 (1_1), U101.39 (TXD0)
BAT_ADC: U101.6 (IO2); also elsewhere on the board
BTN_ACTION: U101.10 (IO6); also elsewhere on the board
BTN_APPROVE: U101.8 (IO4); also elsewhere on the board
BTN_REJECT: U101.9 (IO5); also elsewhere on the board
BTN_WAKE: U101.11 (IO7)
DISP_BL: U101.17 (IO13); also elsewhere on the board
DISP_CS: U101.14 (IO10); also elsewhere on the board
DISP_DC: U101.13 (IO9); also elsewhere on the board
DISP_MOSI: U101.15 (IO11); also elsewhere on the board
DISP_RST: U101.12 (IO8); also elsewhere on the board
DISP_SCLK: U101.16 (IO12); also elsewhere on the board
GND: C101.2, C102.2, C103.2, H101.1 (1_1), SW101.1, TP105.1 (1_1), U101.1 (GND), U101.2 (GND), U101.42 (GND), U101.43 (GND), U101.46 (GND), U101.47 (GND), U101.48 (GND), U101.49 (GND), U101.50 (GND), U101.51 (GND), U101.52 (GND), U101.53 (GND), U101.54 (GND), U101.55 (GND), U101.56 (GND), U101.57 (GND), U101.58 (GND), U101.59 (GND), U101.60 (GND), U101.61 (GND), U101.62 (GND), U101.63 (GND), U101.64 (GND), U101.65 (GND); also elsewhere on the board
LED_PWM: TP104.1 (1_1), U101.34 (IO38); also elsewhere on the board
MOTOR_PWM: U101.33 (IO37); also elsewhere on the board
PWR_CHRG: U101.22 (IO18); also elsewhere on the board
PWR_STDBY: U101.21 (IO17); also elsewhere on the board
USB_DN: U101.23 (USB_D-); also elsewhere on the board
USB_DP: U101.24 (USB_D+); also elsewhere on the board

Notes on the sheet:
BTNS
DISP_SPI
Decoupling_caps
MCU_Enable
PWM
MCU

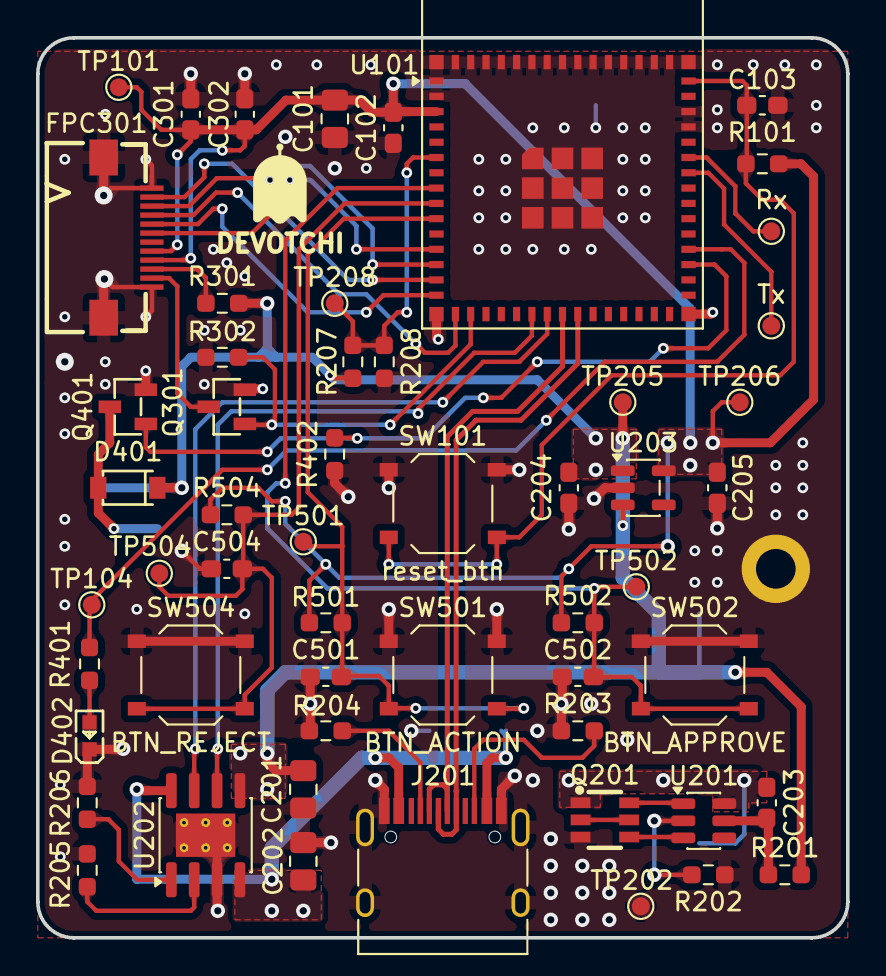
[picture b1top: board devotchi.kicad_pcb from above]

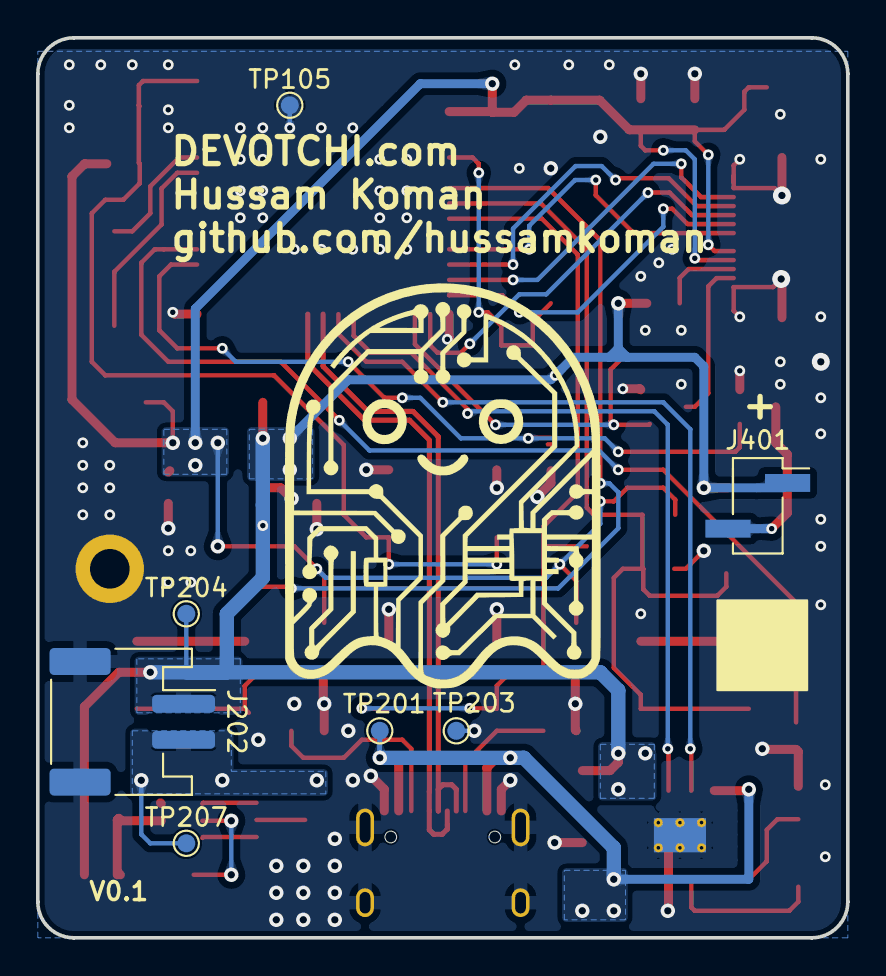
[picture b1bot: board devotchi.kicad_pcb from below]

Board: 4 copper layers, 45.0 x 50.0 mm, 63 parts (7 on the bottom side), 37 nets.

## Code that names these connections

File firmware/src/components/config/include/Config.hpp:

#pragma once

#include "Task.hpp"
#include "driver/gpio.h"
#include <cstddef>
#include <cstdint>

namespace devotchi::config {

namespace pins {
    constexpr gpio_num_t DISP_SCLK    = GPIO_NUM_12;
    constexpr gpio_num_t DISP_MOSI    = GPIO_NUM_11;
    constexpr gpio_num_t DISP_CS      = GPIO_NUM_10;
    constexpr gpio_num_t DISP_DC      = GPIO_NUM_9;
    constexpr gpio_num_t DISP_RST     = GPIO_NUM_8;
    constexpr gpio_num_t DISP_BL      = GPIO_NUM_13;

    constexpr gpio_num_t BTN_APPROVE  = GPIO_NUM_4;
    constexpr gpio_num_t BTN_REJECT   = GPIO_NUM_5;
    constexpr gpio_num_t BTN_ACTION   = GPIO_NUM_6;

    constexpr gpio_num_t LED_PWM      = GPIO_NUM_38;
    constexpr gpio_num_t MOTOR_EN     = GPIO_NUM_37;

    constexpr gpio_num_t PWR_CHRG     = GPIO_NUM_18;
    constexpr gpio_num_t PWR_STDBY    = GPIO_NUM_17;
    constexpr gpio_num_t BAT_ADC      = GPIO_NUM_2;
}

namespace display {
    constexpr int      WIDTH      = 320;
    constexpr int      HEIGHT     = 240;
    constexpr uint32_t SPI_HZ     = 40'000'000;
    constexpr uint32_t BL_PWM_HZ  = 5'000;
}

namespace ui {
    constexpr uint32_t SLEEP_TIMEOUT_MS_DEFAULT = 30'000;
    constexpr uint8_t  BRIGHTNESS_DEFAULT       = 80;
    constexpr uint32_t TICK_INTERVAL_MS         = 33;  // ~30 FPS
}

namespace feedback {
    constexpr uint32_t PWM_HZ       = 5'000;
    constexpr uint8_t  PWM_RES_BITS = 10;     // duty range 0..1023
}

namespace buttons {
    constexpr uint32_t LONG_PRESS_MS  = 1500;
    constexpr std::size_t QUEUE_DEPTH = 8;
}

namespace network {
    constexpr const char* SERVER_HOST        = "10.0.0.120";
    constexpr uint16_t    SERVER_PORT        = 8080;
    constexpr uint32_t    HTTP_TIMEOUT_MS    = 10'000;
    constexpr uint32_t    PAIR_CODE_LEN      = 6;
    constexpr uint32_t    WS_PING_INTERVAL_MS   = 30'000;
    constexpr uint32_t    WS_RECONNECT_DELAY_MS = 5'000;
    constexpr const char* PROV_DEVICE_NAME  = "DEVOTCHI";
    constexpr const char* PROV_POP          = "abcd1234";
}

namespace power {
    constexpr int      BATT_ADC_CHANNEL = 1;          // GPIO 2 = ADC1_CH1 on ESP32-S3
    constexpr uint32_t BATT_VMIN_MV     = 3300;       // 0% at 3.3V
    constexpr uint32_t BATT_VMAX_MV     = 4100;       // 100% at 4.1V
    constexpr uint32_t BATT_DIVIDER_NUM = 2;          // resistor divider 2:1 (verify against schematic)
    constexpr uint32_t BATT_DIVIDER_DEN = 1;
    constexpr uint32_t BATT_SAMPLE_INTERVAL_MS = 5'000;
}

namespace pairing {
    // Alphabet excludes 0/O/I/L/1 to avoid ambiguity (matches server spec).
    constexpr const char* ALPHABET = "ABCDEFGHJKMNPQRSTUVWXYZ23456789";
}

namespace tasks {
    inline constexpr runtime::Task::Spec UI_RENDER = {
        "ui_render",
        8192,
        4,
    };
    inline constexpr runtime::Task::Spec POWER_SAMPLER = {
        "pwr_sample",
        2048,
        2,
    };
}

}  // namespace devotchi::config
